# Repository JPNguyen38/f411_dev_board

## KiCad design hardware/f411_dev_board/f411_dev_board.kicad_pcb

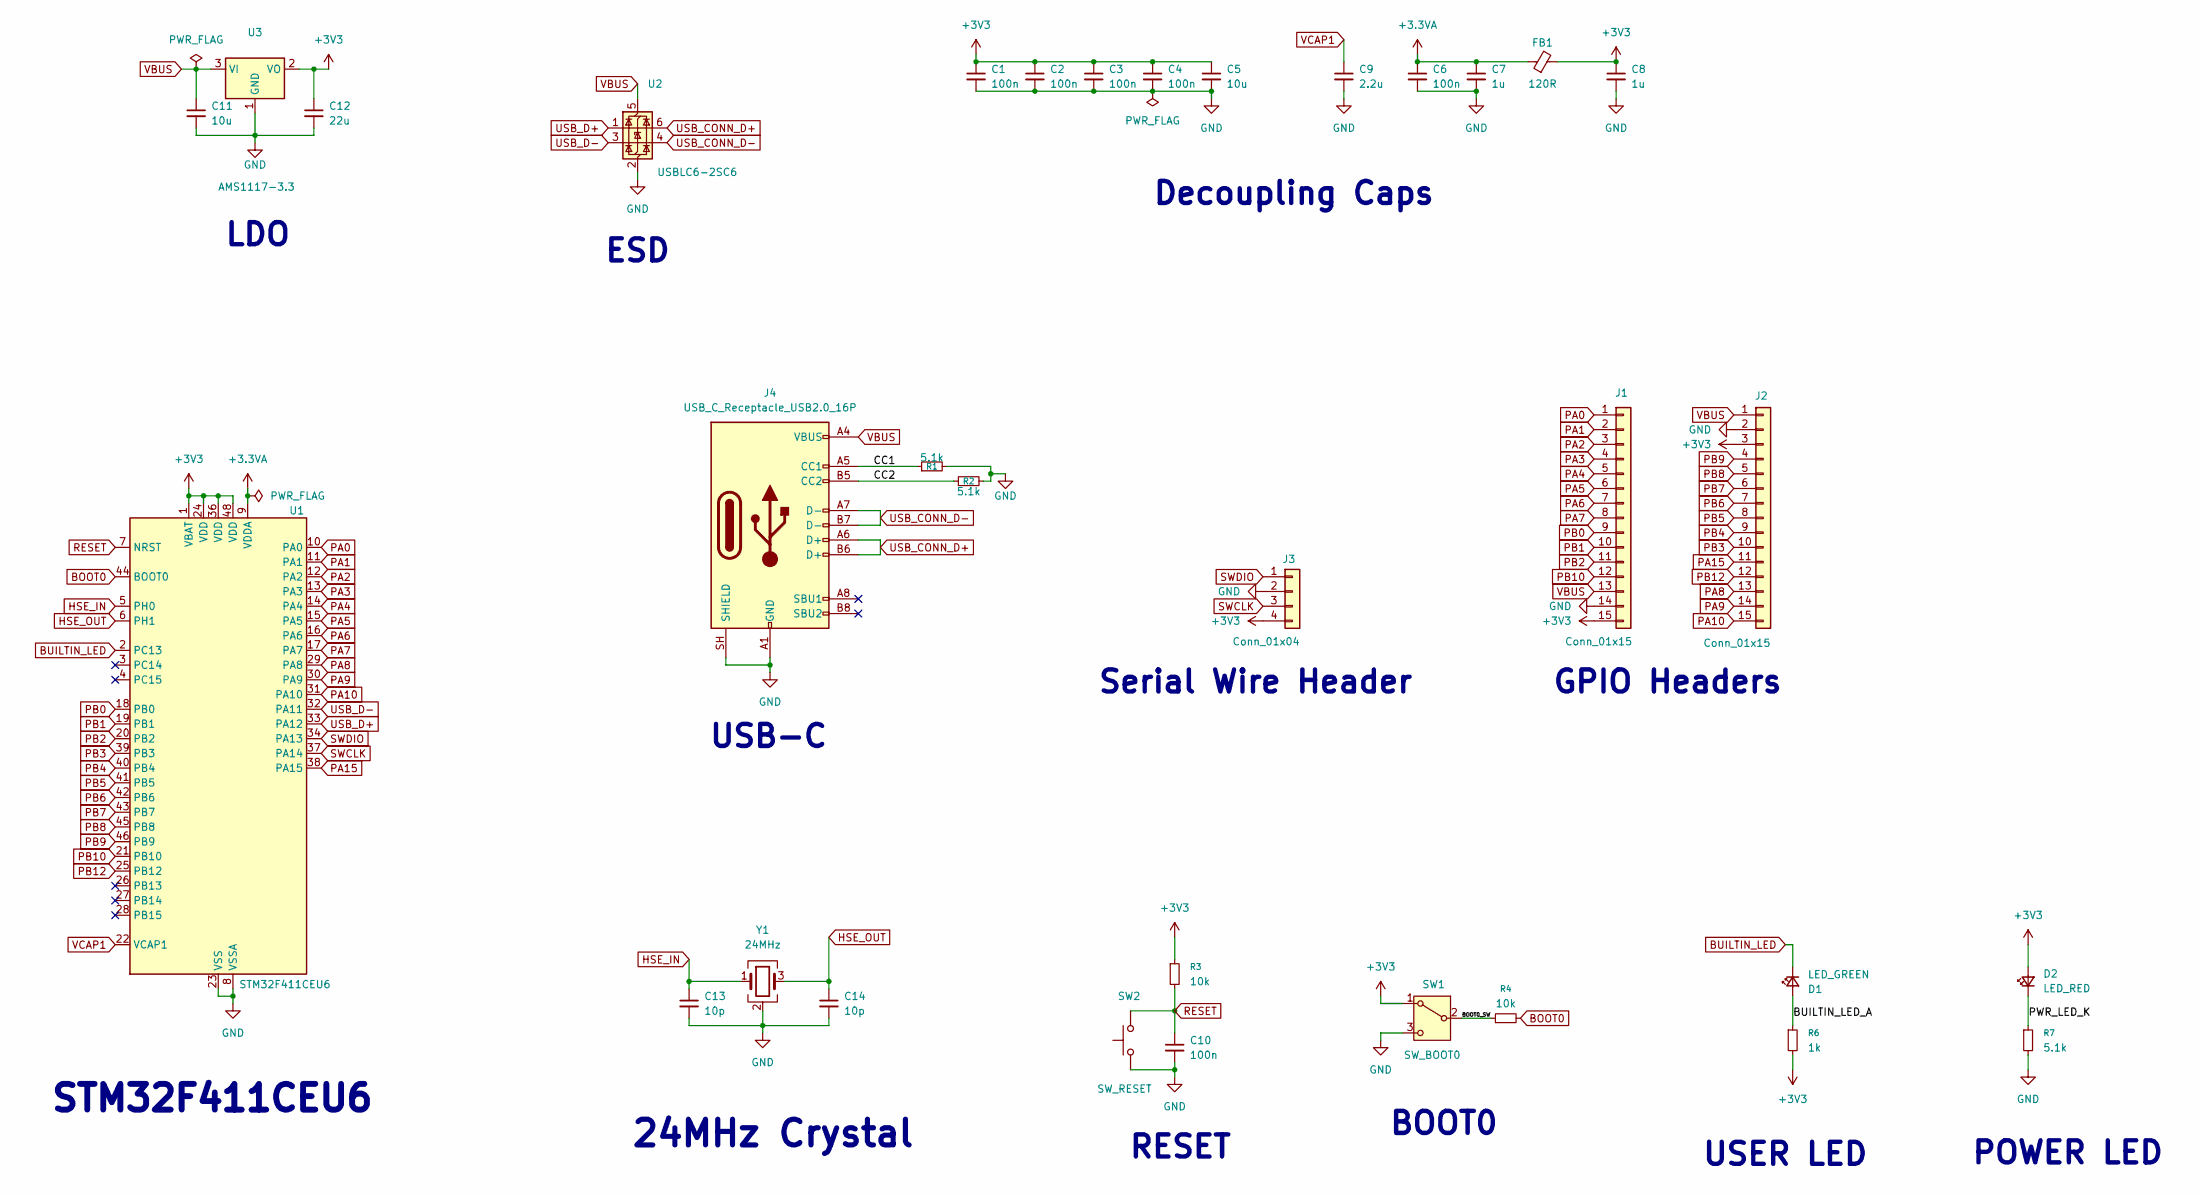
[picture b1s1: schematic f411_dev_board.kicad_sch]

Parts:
C1, C2, C3, C4, C6, C10: 100n; C_0402_1005Metric
C5, C11: 10u; C_0603_1608Metric
C7, C8: 1u; C_0603_1608Metric
C9: 2.2u; C_0603_1608Metric
C12: 22u; C_0603_1608Metric
C13, C14: 10p; C_0402_1005Metric
D1: LED_GREEN; LED_0402_1005Metric
D2: LED_RED; LED_0402_1005Metric
FB1: 120R; L_0603_1608Metric
J1, J2: Conn_01x15; PinHeader_1x15_P2.54mm_Vertical
J3: Conn_01x04; PinHeader_1x04_P2.54mm_Horizontal
J4: USB_C_Receptacle_USB2.0_16P; USB_C_Receptacle_GCT_USB4105-xx-A_16P_TopMnt_Horizontal
R1, R2, R7: 5.1k; R_0402_1005Metric
R3, R4: 10k; R_0402_1005Metric
R6: 1k; R_0402_1005Metric
SW1: SW_BOOT0; SW_Slide_SPDT_Straight_CK_OS102011MS2Q
SW2: SW_RESET; SW_Push_1P1T_XKB_TS-1187A
U1: STM32F411CEU6; QFN-48-1EP_7x7mm_P0.5mm_EP5.6x5.6mm
U2: USBLC6-2SC6; SOT-23-6
U3: AMS1117-3.3; SOT-223-3_TabPin2
Y1: 24MHz; Crystal_SMD_3225-4Pin_3.2x2.5mm

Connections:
+3.3VA: C6.1, C7.1, FB1.1, U1.9 (VDDA)
+3V3: C1.1, C2.1, C3.1, C4.1, C5.1, C8.1, C12.1, D2.2 (A), FB1.2, J1.15, J2.3, J3.4, R3.1, R6.2, SW1.1 (A), U1.1 (VBAT), U1.24 (VDD), U1.36 (VDD), U1.48 (VDD), U3.2 (VO)
/BOOT0_SW: R4.1, SW1.2 (B)
/BUILTIN_LED_A: D1.2 (A), R6.1
/CC1: J4.A5 (CC1), R1.1
/CC2: J4.B5 (CC2), R2.1
/PWR_LED_K: D2.1 (K), R7.1
BOOT0: R4.2, U1.44 (BOOT0)
BUILTIN_LED: D1.1 (K), U1.2 (PC13)
GND: C1.2, C2.2, C3.2, C4.2, C5.2, C6.2, C7.2, C8.2, C9.2, C10.2, C11.2, C12.2, C13.2, C14.2, J1.14, J2.2, J3.2, J4.A1 (GND), J4.A12 (GND), J4.B1 (GND), J4.B12 (GND), J4.SH (SHIELD), R1.2, R2.2, R7.2, SW1.3 (C), SW2.1, U1.8 (VSSA), U1.23 (VSS), U1.35 (VSS), U1.47 (VSS), U1.49 (VSS), U2.2 (GND), U3.1 (GND), Y1.2 (G), Y1.4 (G)
HSE_IN: C13.1, U1.5 (PH0), Y1.1
HSE_OUT: C14.1, U1.6 (PH1), Y1.3
PA0: J1.1, U1.10 (PA0)
PA1: J1.2, U1.11 (PA1)
PA2: J1.3, U1.12 (PA2)
PA3: J1.4, U1.13 (PA3)
PA4: J1.5, U1.14 (PA4)
PA5: J1.6, U1.15 (PA5)
PA6: J1.7, U1.16 (PA6)
PA7: J1.8, U1.17 (PA7)
PA8: J2.13, U1.29 (PA8)
PA9: J2.14, U1.30 (PA9)
PA10: J2.15, U1.31 (PA10)
PA15: J2.11, U1.38 (PA15)
PB0: J1.9, U1.18 (PB0)
PB1: J1.10, U1.19 (PB1)
PB2: J1.11, U1.20 (PB2)
PB3: J2.10, U1.39 (PB3)
PB4: J2.9, U1.40 (PB4)
PB5: J2.8, U1.41 (PB5)
PB6: J2.7, U1.42 (PB6)
PB7: J2.6, U1.43 (PB7)
PB8: J2.5, U1.45 (PB8)
PB9: J2.4, U1.46 (PB9)
PB10: J1.12, U1.21 (PB10)
PB12: J2.12, U1.25 (PB12)
RESET: C10.1, R3.2, SW2.2, U1.7 (NRST)
SWCLK: J3.3, U1.37 (PA14)
SWDIO: J3.1, U1.34 (PA13)
USB_CONN_D+: J4.A6 (D+), J4.B6 (D+), U2.6 (I/O1)
USB_CONN_D-: J4.A7 (D-), J4.B7 (D-), U2.4 (I/O2)
USB_D+: U1.33 (PA12), U2.1 (I/O1)
USB_D-: U1.32 (PA11), U2.3 (I/O2)
VBUS: C11.1, J1.13, J2.1, J4.A4 (VBUS), J4.A9 (VBUS), J4.B4 (VBUS), J4.B9 (VBUS), U2.5 (VBUS), U3.3 (VI)
VCAP1: C9.1, U1.22 (VCAP1)

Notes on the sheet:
USER LED
LDO
RESET
GPIO Headers
ESD
BOOT0
24MHz Crystal
Serial Wire Header
USB-C
POWER LED
STM32F411CEU6
Decoupling Caps

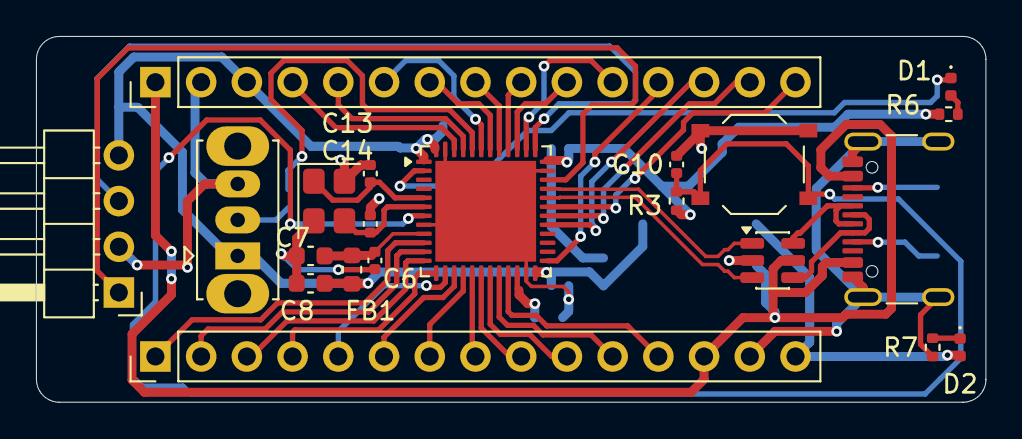
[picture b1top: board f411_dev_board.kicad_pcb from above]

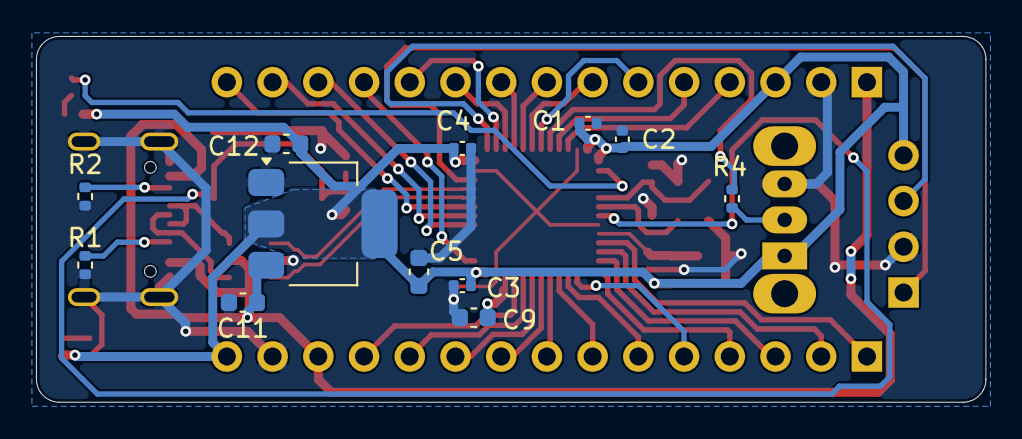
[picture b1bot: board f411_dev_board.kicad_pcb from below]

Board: 2 copper layers, 52.8 x 20.3 mm, 33 parts (12 on the bottom side), 45 nets.

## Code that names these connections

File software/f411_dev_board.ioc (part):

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Mcu.Name=STM32F411C(C-E)Ux
Mcu.Package=UFQFPN48
Mcu.UserName=STM32F411CEUx
PA11.Mode=Device_Only
PA11.Signal=USB_OTG_FS_DM
PA12.Mode=Device_Only
PA12.Signal=USB_OTG_FS_DP
PA13.Mode=Serial_Wire
PA13.Signal=SYS_JTMS-SWDIO
PA14.Mode=Serial_Wire
PA14.Signal=SYS_JTCK-SWCLK
PH0\ -\ OSC_IN.Mode=HSE-External-Oscillator
PH0\ -\ OSC_IN.Signal=RCC_OSC_IN
PH1\ -\ OSC_OUT.Mode=HSE-External-Oscillator
PH1\ -\ OSC_OUT.Signal=RCC_OSC_OUT
RCC.HSE_VALUE=24000000
RCC.SYSCLKFreq_VALUE=16000000
board=custom
